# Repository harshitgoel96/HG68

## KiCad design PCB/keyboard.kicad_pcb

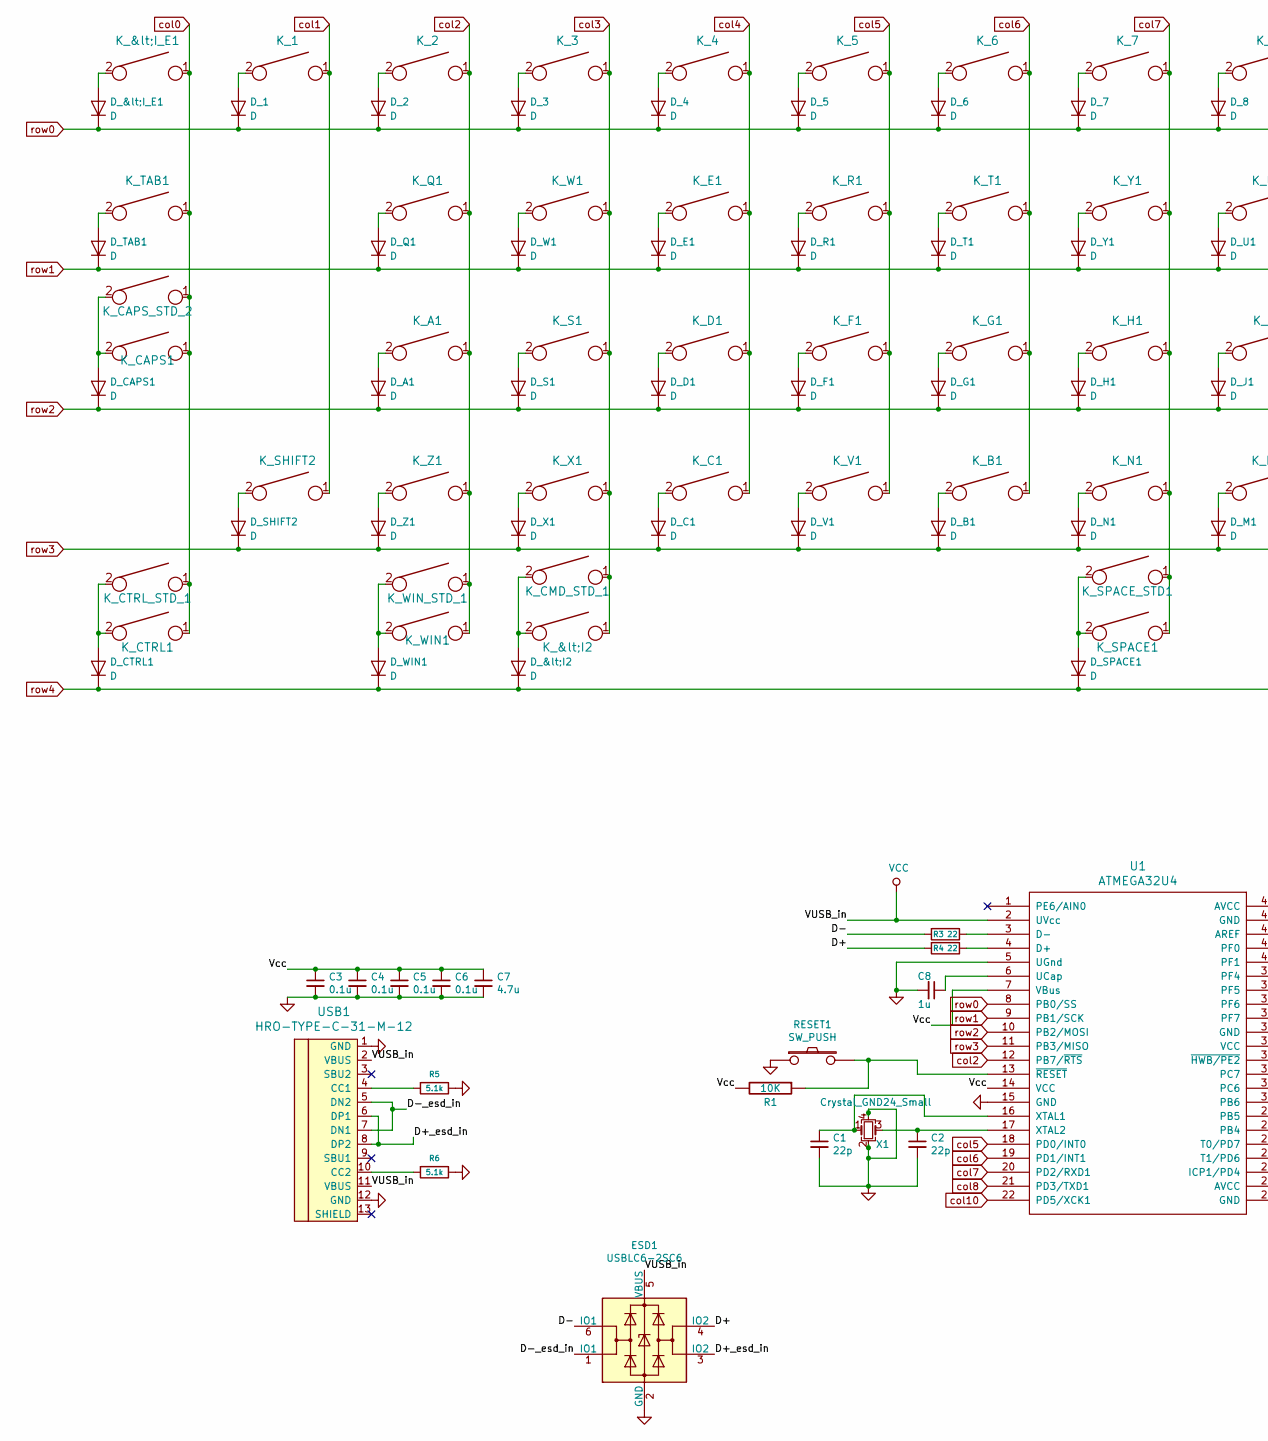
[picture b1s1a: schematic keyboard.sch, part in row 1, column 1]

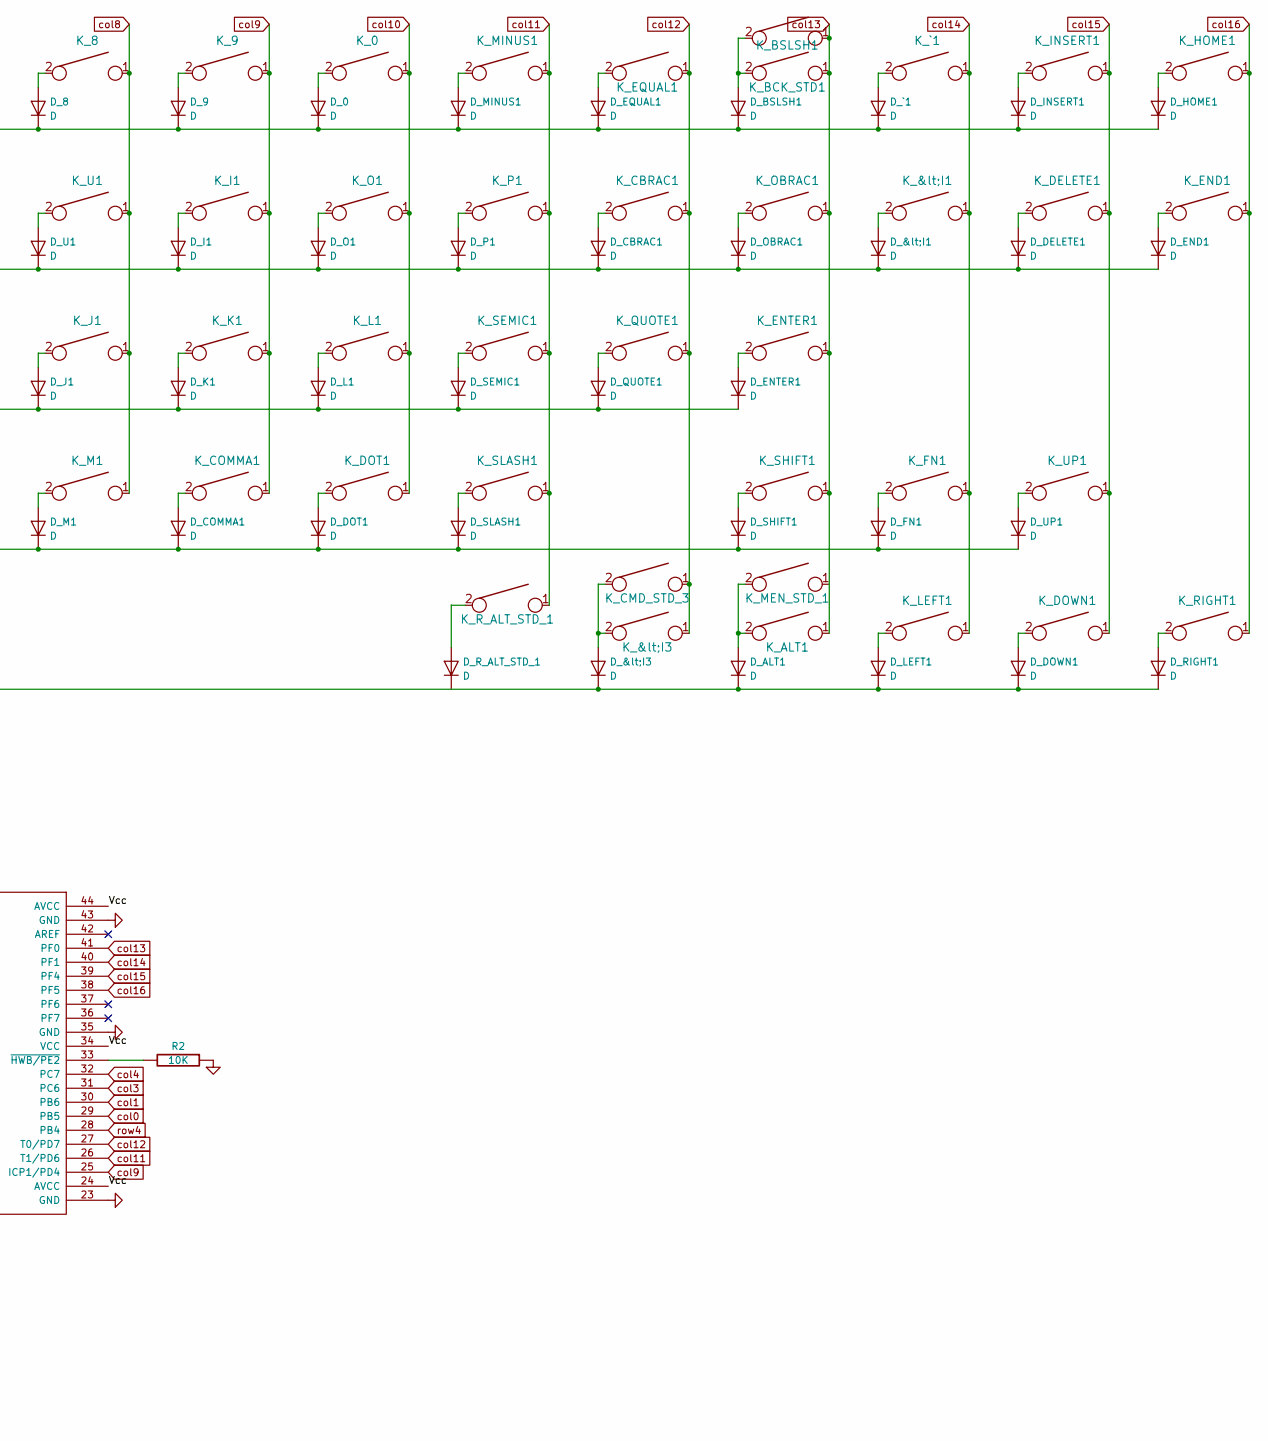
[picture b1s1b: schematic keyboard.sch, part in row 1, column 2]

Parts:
C1, C2: 22p; C_0805_2012Metric_Pad1.15x1.40mm_HandSolder
C3, C4, C5, C6: 0.1u; C_0805_2012Metric_Pad1.15x1.40mm_HandSolder
C7: 4.7u; C_0805_2012Metric_Pad1.15x1.40mm_HandSolder
C8: 1u; C_0805_2012Metric_Pad1.15x1.40mm_HandSolder
D_0, D_1, D_2, D_3, D_4, D_5, D_6, D_7, D_8, D_9: D; D_SOD-123
D_&lt;I1, D_&lt;I2, D_&lt;I3: D; D_SOD-123
D_&lt;I_E1: D; D_SOD-123
D_A1: D; D_SOD-123
D_ALT1: D; D_SOD-123
D_B1: D; D_SOD-123
D_BSLSH1: D; D_SOD-123
D_C1: D; D_SOD-123
D_CAPS1: D; D_SOD-123
D_CBRAC1: D; D_SOD-123
D_COMMA1: D; D_SOD-123
D_CTRL1: D; D_SOD-123
D_D1: D; D_SOD-123
D_DELETE1: D; D_SOD-123
D_DOT1: D; D_SOD-123
D_DOWN1: D; D_SOD-123
D_E1: D; D_SOD-123
D_END1: D; D_SOD-123
D_ENTER1: D; D_SOD-123
D_EQUAL1: D; D_SOD-123
D_F1: D; D_SOD-123
D_FN1: D; D_SOD-123
D_G1: D; D_SOD-123
D_H1: D; D_SOD-123
D_HOME1: D; D_SOD-123
D_I1: D; D_SOD-123
D_INSERT1: D; D_SOD-123
D_J1: D; D_SOD-123
D_K1: D; D_SOD-123
D_L1: D; D_SOD-123
D_LEFT1: D; D_SOD-123
D_M1: D; D_SOD-123
D_MINUS1: D; D_SOD-123
D_N1: D; D_SOD-123
D_O1: D; D_SOD-123
D_OBRAC1: D; D_SOD-123
D_P1: D; D_SOD-123
D_Q1: D; D_SOD-123
D_QUOTE1: D; D_SOD-123
D_R1: D; D_SOD-123
D_RIGHT1: D; D_SOD-123
D_R_ALT_STD_1: D; D_SOD-123
D_S1: D; D_SOD-123
D_SEMIC1: D; D_SOD-123
D_SHIFT1, D_SHIFT2: D; D_SOD-123
D_SLASH1: D; D_SOD-123
D_SPACE1: D; D_SOD-123
D_T1: D; D_SOD-123
D_TAB1: D; D_SOD-123
D_U1: D; D_SOD-123
D_UP1: D; D_SOD-123
D_V1: D; D_SOD-123
D_W1: D; D_SOD-123
D_WIN1: D; D_SOD-123
D_X1: D; D_SOD-123
D_Y1: D; D_SOD-123
D_Z1: D; D_SOD-123
D_`1: D; D_SOD-123
ESD1: USBLC6-2SC6; SOT-23-6
K_0, K_1, K_2, K_3, K_4, K_5, K_6, K_7, K_8, K_9: KEYSW; MXOnly-1U-NoLED
K_&lt;I1, K_&lt;I2, K_&lt;I3: KEYSW; MXOnly-1.5U-NoLED
K_&lt;I_E1: KEYSW; MXOnly-1U-NoLED
K_A1: KEYSW; MXOnly-1U-NoLED
K_ALT1: KEYSW; MXOnly-1.25U-NoLED
K_B1: KEYSW; MXOnly-1U-NoLED
K_BCK_STD1: KEYSW; MXOnly-2U-NoLED
K_BSLSH1: KEYSW; MXOnly-1U-NoLED
K_C1: KEYSW; MXOnly-1U-NoLED
K_CAPS1: KEYSW; MXOnly-1.25U-NoLED
K_CAPS_STD_2: KEYSW; MXOnly-1.75U-NoLED
K_CBRAC1: KEYSW; MXOnly-1U-NoLED
K_CMD_STD_1, K_CMD_STD_3: KEYSW; MXOnly-1.25U-NoLED
K_COMMA1: KEYSW; MXOnly-1U-NoLED
K_CTRL1: KEYSW; MXOnly-1.5U-NoLED
K_CTRL_STD_1: KEYSW; MXOnly-1.25U-NoLED
K_D1: KEYSW; MXOnly-1U-NoLED
K_DELETE1: KEYSW; MXOnly-1U-NoLED
K_DOT1: KEYSW; MXOnly-1U-NoLED
K_DOWN1: KEYSW; MXOnly-1U-NoLED
K_E1: KEYSW; MXOnly-1U-NoLED
K_END1: KEYSW; MXOnly-1U-NoLED
K_ENTER1: KEYSW; MXOnly-2.25U-NoLED
K_EQUAL1: KEYSW; MXOnly-1U-NoLED
K_F1: KEYSW; MXOnly-1U-NoLED
K_FN1: KEYSW; MXOnly-1U-NoLED
K_G1: KEYSW; MXOnly-1U-NoLED
K_H1: KEYSW; MXOnly-1U-NoLED
K_HOME1: KEYSW; MXOnly-1U-NoLED
K_I1: KEYSW; MXOnly-1U-NoLED
K_INSERT1: KEYSW; MXOnly-1U-NoLED
K_J1: KEYSW; MXOnly-1U-NoLED
K_K1: KEYSW; MXOnly-1U-NoLED
K_L1: KEYSW; MXOnly-1U-NoLED
K_LEFT1: KEYSW; MXOnly-1U-NoLED
K_M1: KEYSW; MXOnly-1U-NoLED
K_MEN_STD_1: KEYSW; MXOnly-1.25U-NoLED
K_MINUS1: KEYSW; MXOnly-1U-NoLED
K_N1: KEYSW; MXOnly-1U-NoLED
K_O1: KEYSW; MXOnly-1U-NoLED
K_OBRAC1: KEYSW; MXOnly-1U-NoLED
K_P1: KEYSW; MXOnly-1U-NoLED
K_Q1: KEYSW; MXOnly-1U-NoLED
K_QUOTE1: KEYSW; MXOnly-1U-NoLED
K_R1: KEYSW; MXOnly-1U-NoLED
K_RIGHT1: KEYSW; MXOnly-1U-NoLED
K_R_ALT_STD_1: KEYSW; MXOnly-1.25U-NoLED
K_S1: KEYSW; MXOnly-1U-NoLED
K_SEMIC1: KEYSW; MXOnly-1U-NoLED
K_SHIFT1: KEYSW; MXOnly-1.75U-NoLED
K_SHIFT2: KEYSW; MXOnly-2.25U-NoLED
K_SLASH1: KEYSW; MXOnly-1U-NoLED
K_SPACE1: KEYSW; MXOnly-7U-NoLED
K_SPACE_STD1: KEYSW; MXOnly-6.25U-NoLED
K_T1: KEYSW; MXOnly-1U-NoLED
K_TAB1: KEYSW; MXOnly-1.5U-NoLED
K_U1: KEYSW; MXOnly-1U-NoLED
K_UP1: KEYSW; MXOnly-1U-NoLED
K_V1: KEYSW; MXOnly-1U-NoLED
K_W1: KEYSW; MXOnly-1U-NoLED
K_WIN1: KEYSW; MXOnly-1.25U-NoLED
K_WIN_STD_1: KEYSW; MXOnly-1.25U-NoLED
K_X1: KEYSW; MXOnly-1U-NoLED
K_Y1: KEYSW; MXOnly-1U-NoLED
K_Z1: KEYSW; MXOnly-1U-NoLED
K_`1: KEYSW; MXOnly-1U-NoLED
R1, R2: 10K; R_0805_2012Metric_Pad1.15x1.40mm_HandSolder
R3, R4: 22; R_0805_2012Metric_Pad1.15x1.40mm_HandSolder
R5, R6: 5.1k; R_0805_2012Metric_Pad1.15x1.40mm_HandSolder
RESET1: SW_PUSH; SW_SPST_TL3342
U1: ATMEGA32U4; TQFP-44_10x10mm_P0.8mm
USB1: HRO-TYPE-C-31-M-12
X1: Crystal_GND24_Small; Crystal_SMD_5032-4Pin-HandSolder

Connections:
/D+: ESD1.4 (IO2), R4.2
/D+_esd_in: ESD1.3 (IO2), USB1.6 (DP1), USB1.8 (DP2)
/D-: ESD1.6 (IO1), R3.2
/D-_esd_in: ESD1.1 (IO1), USB1.5 (DN2), USB1.7 (DN1)
/Vcc: C3.1, C4.1, C5.1, C6.1, C7.1, R1.2, U1.7 (VBus), U1.14 (VCC), U1.24 (AVCC), U1.34 (VCC), U1.44 (AVCC)
GND: C1.2, C2.2, C3.2, C4.2, C5.2, C6.2, C7.2, C8.2, ESD1.2 (GND), R2.1, R5.1, R6.1, RESET1.1, U1.5 (UGnd), U1.15 (GND), U1.23 (GND), U1.35 (GND), U1.43 (GND), USB1.1 (GND), USB1.12 (GND), X1.2, X1.4
unnamed: C1.1, U1.16 (XTAL1), X1.1
unnamed: C2.1, U1.17 (XTAL2), X1.3
unnamed: C8.1, U1.6 (UCap)
unnamed: D_0.2 (A), K_0.2
unnamed: D_1.2 (A), K_1.2
unnamed: D_2.2 (A), K_2.2
unnamed: D_3.2 (A), K_3.2
unnamed: D_4.2 (A), K_4.2
unnamed: D_5.2 (A), K_5.2
unnamed: D_6.2 (A), K_6.2
unnamed: D_7.2 (A), K_7.2
unnamed: D_8.2 (A), K_8.2
unnamed: D_9.2 (A), K_9.2
unnamed: D_&lt;I1.2 (A), K_&lt;I1.2
unnamed: D_&lt;I2.2 (A), K_&lt;I2.2, K_CMD_STD_1.2
unnamed: D_&lt;I3.2 (A), K_&lt;I3.2, K_CMD_STD_3.2
unnamed: D_&lt;I_E1.2 (A), K_&lt;I_E1.2
unnamed: D_A1.2 (A), K_A1.2
unnamed: D_ALT1.2 (A), K_ALT1.2, K_MEN_STD_1.2
unnamed: D_B1.2 (A), K_B1.2
unnamed: D_BSLSH1.2 (A), K_BCK_STD1.2, K_BSLSH1.2
unnamed: D_C1.2 (A), K_C1.2
unnamed: D_CAPS1.2 (A), K_CAPS1.2, K_CAPS_STD_2.2
unnamed: D_CBRAC1.2 (A), K_CBRAC1.2
unnamed: D_COMMA1.2 (A), K_COMMA1.2
unnamed: D_CTRL1.2 (A), K_CTRL1.2, K_CTRL_STD_1.2
unnamed: D_D1.2 (A), K_D1.2
unnamed: D_DELETE1.2 (A), K_DELETE1.2
unnamed: D_DOT1.2 (A), K_DOT1.2
unnamed: D_DOWN1.2 (A), K_DOWN1.2
unnamed: D_E1.2 (A), K_E1.2
unnamed: D_END1.2 (A), K_END1.2
unnamed: D_ENTER1.2 (A), K_ENTER1.2
unnamed: D_EQUAL1.2 (A), K_EQUAL1.2
unnamed: D_F1.2 (A), K_F1.2
unnamed: D_FN1.2 (A), K_FN1.2
unnamed: D_G1.2 (A), K_G1.2
unnamed: D_H1.2 (A), K_H1.2
unnamed: D_HOME1.2 (A), K_HOME1.2
unnamed: D_I1.2 (A), K_I1.2
unnamed: D_INSERT1.2 (A), K_INSERT1.2
unnamed: D_J1.2 (A), K_J1.2
unnamed: D_K1.2 (A), K_K1.2
unnamed: D_L1.2 (A), K_L1.2
unnamed: D_LEFT1.2 (A), K_LEFT1.2
unnamed: D_M1.2 (A), K_M1.2
unnamed: D_MINUS1.2 (A), K_MINUS1.2
unnamed: D_N1.2 (A), K_N1.2
unnamed: D_O1.2 (A), K_O1.2
unnamed: D_OBRAC1.2 (A), K_OBRAC1.2
unnamed: D_P1.2 (A), K_P1.2
unnamed: D_Q1.2 (A), K_Q1.2
unnamed: D_QUOTE1.2 (A), K_QUOTE1.2
unnamed: D_R1.2 (A), K_R1.2
unnamed: D_RIGHT1.2 (A), K_RIGHT1.2
unnamed: D_R_ALT_STD_1.2 (A), K_R_ALT_STD_1.2
unnamed: D_S1.2 (A), K_S1.2
unnamed: D_SEMIC1.2 (A), K_SEMIC1.2
unnamed: D_SHIFT1.2 (A), K_SHIFT1.2
unnamed: D_SHIFT2.2 (A), K_SHIFT2.2
unnamed: D_SLASH1.2 (A), K_SLASH1.2
unnamed: D_SPACE1.2 (A), K_SPACE1.2, K_SPACE_STD1.2
unnamed: D_T1.2 (A), K_T1.2
unnamed: D_TAB1.2 (A), K_TAB1.2
unnamed: D_U1.2 (A), K_U1.2
unnamed: D_UP1.2 (A), K_UP1.2
unnamed: D_V1.2 (A), K_V1.2
unnamed: D_W1.2 (A), K_W1.2
unnamed: D_WIN1.2 (A), K_WIN1.2, K_WIN_STD_1.2
unnamed: D_X1.2 (A), K_X1.2
unnamed: D_Y1.2 (A), K_Y1.2
unnamed: D_Z1.2 (A), K_Z1.2
unnamed: D_`1.2 (A), K_`1.2
unnamed: R1.1, RESET1.2, U1.13 (~RESET)
unnamed: R2.2, U1.33 (~HWB/PE2)
unnamed: R3.1, U1.3 (D-)
unnamed: R4.1, U1.4 (D+)
unnamed: R5.2, USB1.4 (CC1)
unnamed: R6.2, USB1.10 (CC2)
VCC: ESD1.5 (VBUS), U1.2 (UVcc), USB1.2 (VBUS), USB1.11 (VBUS)
col0: K_&lt;I_E1.1, K_CAPS1.1, K_CAPS_STD_2.1, K_CTRL1.1, K_CTRL_STD_1.1, K_TAB1.1, U1.29 (PB5)
col1: K_1.1, K_SHIFT2.1, U1.30 (PB6)
col2: K_2.1, K_A1.1, K_Q1.1, K_WIN1.1, K_WIN_STD_1.1, K_Z1.1, U1.12 (PB7/~RTS)
col3: K_3.1, K_&lt;I2.1, K_CMD_STD_1.1, K_S1.1, K_W1.1, K_X1.1, U1.31 (PC6)
col4: K_4.1, K_C1.1, K_D1.1, K_E1.1, U1.32 (PC7)
col5: K_5.1, K_F1.1, K_R1.1, K_V1.1, U1.18 (PD0/INT0)
col6: K_6.1, K_B1.1, K_G1.1, K_T1.1, U1.19 (PD1/INT1)
col7: K_7.1, K_H1.1, K_N1.1, K_SPACE1.1, K_SPACE_STD1.1, K_Y1.1, U1.20 (PD2/RXD1)
col8: K_8.1, K_J1.1, K_M1.1, K_U1.1, U1.21 (PD3/TXD1)
col9: K_9.1, K_COMMA1.1, K_I1.1, K_K1.1, U1.25 (ICP1/PD4)
col10: K_0.1, K_DOT1.1, K_L1.1, K_O1.1, U1.22 (PD5/XCK1)
col11: K_MINUS1.1, K_P1.1, K_R_ALT_STD_1.1, K_SEMIC1.1, K_SLASH1.1, U1.26 (T1/PD6)
col12: K_&lt;I3.1, K_CBRAC1.1, K_CMD_STD_3.1, K_EQUAL1.1, K_QUOTE1.1, U1.27 (T0/PD7)
col13: K_ALT1.1, K_BCK_STD1.1, K_BSLSH1.1, K_ENTER1.1, K_OBRAC1.1, K_SHIFT1.1, U1.41 (PF0)
col14: K_&lt;I1.1, K_FN1.1, K_LEFT1.1, K_`1.1, U1.40 (PF1)
col15: K_DELETE1.1, K_DOWN1.1, K_INSERT1.1, K_UP1.1, U1.39 (PF4)
col16: K_END1.1, K_HOME1.1, K_RIGHT1.1, U1.38 (PF5)
row0: D_0.1 (K), D_1.1 (K), D_2.1 (K), D_3.1 (K), D_4.1 (K), D_5.1 (K), D_6.1 (K), D_7.1 (K), D_8.1 (K), D_9.1 (K), D_&lt;I_E1.1 (K), D_BSLSH1.1 (K), D_EQUAL1.1 (K), D_HOME1.1 (K), D_INSERT1.1 (K), D_MINUS1.1 (K), D_`1.1 (K), U1.8 (PB0/SS)
row1: D_&lt;I1.1 (K), D_CBRAC1.1 (K), D_DELETE1.1 (K), D_E1.1 (K), D_END1.1 (K), D_I1.1 (K), D_O1.1 (K), D_OBRAC1.1 (K), D_P1.1 (K), D_Q1.1 (K), D_R1.1 (K), D_T1.1 (K), D_TAB1.1 (K), D_U1.1 (K), D_W1.1 (K), D_Y1.1 (K), U1.9 (PB1/SCK)
row2: D_A1.1 (K), D_CAPS1.1 (K), D_D1.1 (K), D_ENTER1.1 (K), D_F1.1 (K), D_G1.1 (K), D_H1.1 (K), D_J1.1 (K), D_K1.1 (K), D_L1.1 (K), D_QUOTE1.1 (K), D_S1.1 (K), D_SEMIC1.1 (K), U1.10 (PB2/MOSI)
row3: D_B1.1 (K), D_C1.1 (K), D_COMMA1.1 (K), D_DOT1.1 (K), D_FN1.1 (K), D_M1.1 (K), D_N1.1 (K), D_SHIFT1.1 (K), D_SHIFT2.1 (K), D_SLASH1.1 (K), D_UP1.1 (K), D_V1.1 (K), D_X1.1 (K), D_Z1.1 (K), U1.11 (PB3/MISO)
row4: D_&lt;I2.1 (K), D_&lt;I3.1 (K), D_ALT1.1 (K), D_CTRL1.1 (K), D_DOWN1.1 (K), D_LEFT1.1 (K), D_RIGHT1.1 (K), D_SPACE1.1 (K), D_WIN1.1 (K), U1.28 (PB4)

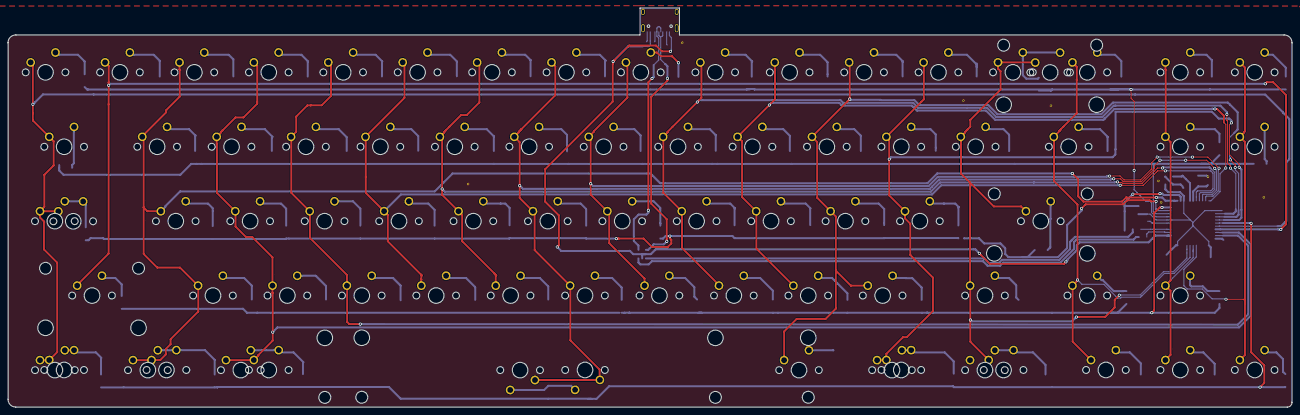
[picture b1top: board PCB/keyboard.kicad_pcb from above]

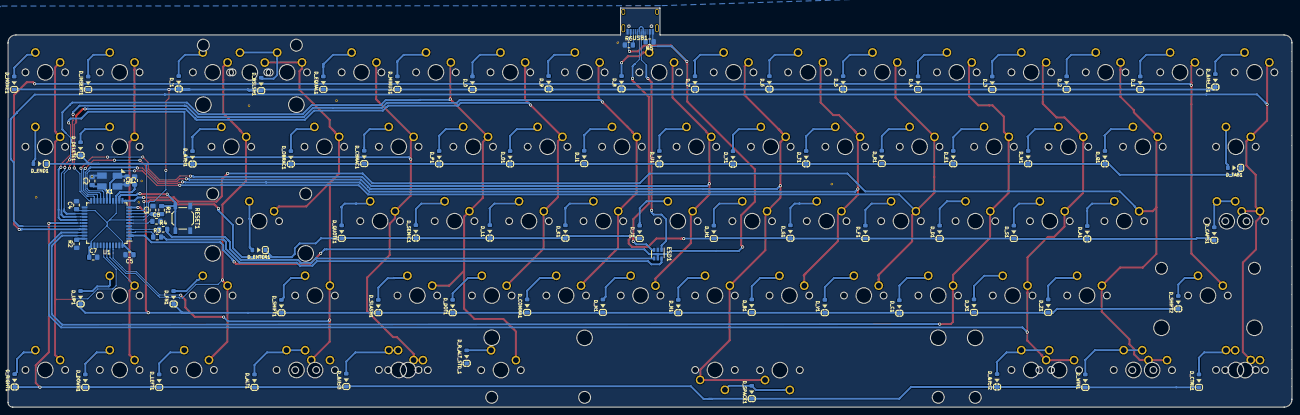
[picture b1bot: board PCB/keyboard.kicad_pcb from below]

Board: 2 copper layers, 328.7 x 102.2 mm, 167 parts (89 on the bottom side), 108 nets.

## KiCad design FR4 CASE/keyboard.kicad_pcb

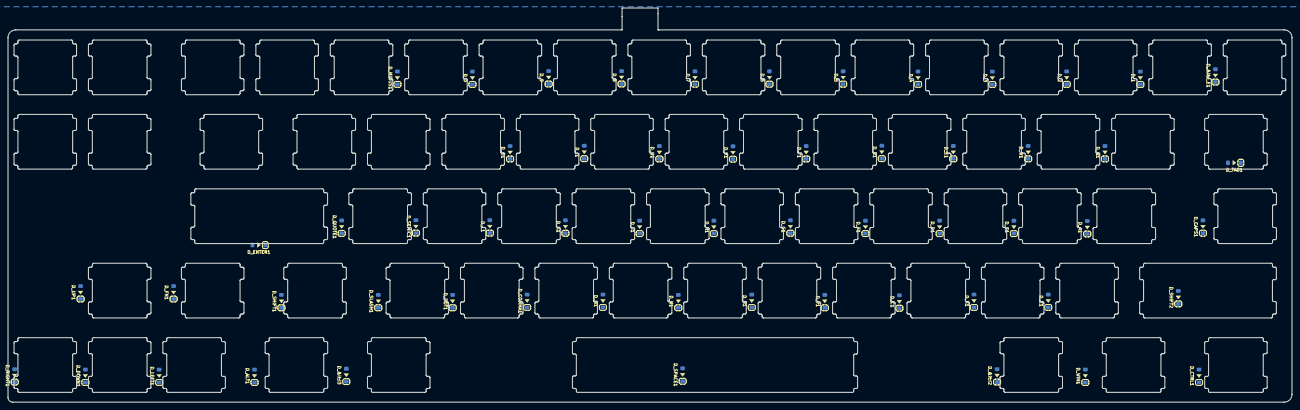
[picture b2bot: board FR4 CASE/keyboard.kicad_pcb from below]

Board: 2 copper layers, 328.7 x 100.9 mm, 127 parts (58 on the bottom side), 6 nets, no tracks yet.

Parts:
D_0, D_1, D_2, D_3, D_4, D_5, D_6, D_7, D_8, D_9: D; D_SOD-123
D_&lt;I2, D_&lt;I3: D; D_SOD-123
D_&lt;I_E1: D; D_SOD-123
D_A1: D; D_SOD-123
D_ALT1: D; D_SOD-123
D_B1: D; D_SOD-123
D_C1: D; D_SOD-123
D_CAPS1: D; D_SOD-123
D_COMMA1: D; D_SOD-123
D_CTRL1: D; D_SOD-123
D_D1: D; D_SOD-123
D_DOT1: D; D_SOD-123
D_DOWN1: D; D_SOD-123
D_E1: D; D_SOD-123
D_ENTER1: D; D_SOD-123
D_F1: D; D_SOD-123
D_FN1: D; D_SOD-123
D_G1: D; D_SOD-123
D_H1: D; D_SOD-123
D_I1: D; D_SOD-123
D_J1: D; D_SOD-123
D_K1: D; D_SOD-123
D_L1: D; D_SOD-123
D_LEFT1: D; D_SOD-123
D_M1: D; D_SOD-123
D_MINUS1: D; D_SOD-123
D_N1: D; D_SOD-123
D_O1: D; D_SOD-123
D_Q1: D; D_SOD-123
D_QUOTE1: D; D_SOD-123
D_R1: D; D_SOD-123
D_RIGHT1: D; D_SOD-123
D_S1: D; D_SOD-123
D_SEMIC1: D; D_SOD-123
D_SHIFT1, D_SHIFT2: D; D_SOD-123
D_SLASH1: D; D_SOD-123
D_SPACE1: D; D_SOD-123
D_T1: D; D_SOD-123
D_TAB1: D; D_SOD-123
D_U1: D; D_SOD-123
D_UP1: D; D_SOD-123
D_V1: D; D_SOD-123
D_W1: D; D_SOD-123
D_WIN1: D; D_SOD-123
D_X1: D; D_SOD-123
D_Y1: D; D_SOD-123
D_Z1: D; D_SOD-123
K_0, K_1, K_2, K_3, K_4, K_5, K_6, K_7, K_8, K_9: KEYSW; slotMX100
K_&lt;I1, K_&lt;I2, K_&lt;I3: KEYSW; slotMX100
K_&lt;I_E1: KEYSW; slotMX100
K_A1: KEYSW; slotMX100
K_ALT1: KEYSW; slotMX100
K_B1: KEYSW; slotMX100
K_BSLSH1: KEYSW; slotMX100
K_C1: KEYSW; slotMX100
K_CAPS1: KEYSW; slotMX100
K_CBRAC1: KEYSW; slotMX100
K_COMMA1: KEYSW; slotMX100
K_CTRL1: KEYSW; slotMX100
K_D1: KEYSW; slotMX100
K_DELETE1: KEYSW; slotMX100
K_DOT1: KEYSW; slotMX100
K_DOWN1: KEYSW; slotMX100
K_E1: KEYSW; slotMX100
K_END1: KEYSW; slotMX100
K_ENTER1: KEYSW; slotMX200
K_EQUAL1: KEYSW; slotMX100
K_F1: KEYSW; slotMX100
K_FN1: KEYSW; slotMX100
K_G1: KEYSW; slotMX100
K_H1: KEYSW; slotMX100
K_HOME1: KEYSW; slotMX100
K_I1: KEYSW; slotMX100
K_INSERT1: KEYSW; slotMX100
K_J1: KEYSW; slotMX100
K_K1: KEYSW; slotMX100
K_L1: KEYSW; slotMX100
K_LEFT1: KEYSW; slotMX100
K_M1: KEYSW; slotMX100
K_MINUS1: KEYSW; slotMX100
K_N1: KEYSW; slotMX100
K_O1: KEYSW; slotMX100
K_OBRAC1: KEYSW; slotMX100
K_P1: KEYSW; slotMX100
K_Q1: KEYSW; slotMX100
K_QUOTE1: KEYSW; slotMX100
K_R1: KEYSW; slotMX100
K_RIGHT1: KEYSW; slotMX100
K_S1: KEYSW; slotMX100
K_SEMIC1: KEYSW; slotMX100
K_SHIFT1: KEYSW; slotMX100
K_SHIFT2: KEYSW; slotMX200
K_SLASH1: KEYSW; slotMX100
K_SPACE1: KEYSW; slotMX400
K_T1: KEYSW; slotMX100
K_TAB1: KEYSW; slotMX100
K_U1: KEYSW; slotMX100
K_UP1: KEYSW; slotMX100
K_V1: KEYSW; slotMX100
K_W1: KEYSW; slotMX100
K_WIN1: KEYSW; slotMX100
K_X1: KEYSW; slotMX100
K_Y1: KEYSW; slotMX100
K_Z1: KEYSW; slotMX100
K_`1: KEYSW; slotMX100

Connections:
unnamed: D_&lt;I3.1, D_ALT1.1, D_DOWN1.1, D_LEFT1.1, D_RIGHT1.1, D_SPACE1.1
unnamed: D_A1.1, D_D1.1, D_ENTER1.1, D_F1.1, D_G1.1, D_H1.1, D_J1.1, D_K1.1, D_L1.1, D_QUOTE1.1, D_S1.1, D_SEMIC1.1
unnamed: D_B1.1, D_C1.1, D_COMMA1.1, D_DOT1.1, D_FN1.1, D_M1.1, D_N1.1, D_SHIFT1.1, D_SLASH1.1, D_UP1.1, D_V1.1
unnamed: D_E1.1, D_I1.1, D_O1.1, D_Q1.1, D_R1.1, D_T1.1, D_U1.1, D_W1.1, D_Y1.1
row3: D_SHIFT2.1, D_X1.1, D_Z1.1
row4: D_&lt;I2.1, D_CTRL1.1, D_WIN1.1

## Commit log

2019-10-17 added standard 68 key layout
2019-10-17 added usb type c.
